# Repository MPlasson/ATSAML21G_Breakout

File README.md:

# ATSAML21G_Breakout
Breakout board for ATSAML21Gxx MCU

Now available on PCBS.io (sharing link): 
https://pcbs.io/share/rG9PZ

Bill of materials (BOM):

|  Designator  | Value |  Package description |
|     :---:      |     :---:      |     :---:      |
|R1 | 10k | 0805 |
|C1 | 100nF | 0805 |
|C2 | 1µF | 0805 |
|C3 | 100nF | 0805 |
|C4 | 1µF | 0805 |
|J1 | 21 pins | 0.1"/2.54mm header |
|J2 | 20 pins | 0.1"/2.54mm header |
|J3 | 5 pins | 0.1"/2.54mm header - JTAG connector |
|SW1 | K2-1107ST | Switch from LCSC.com |
|U1 | ATSAML21Gxx | MCU in LQFP48 package |

Here is the board once assembled:

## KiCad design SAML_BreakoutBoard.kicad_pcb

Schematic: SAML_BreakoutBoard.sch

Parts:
C1, C3: 100nF; C_0805
C2, C4: 1µF; C_0805
J1: Conn_01x21; Pin_Header_Straight_1x21_Pitch2.54mm
J2: Conn_01x20; Pin_Header_Straight_1x20_Pitch2.54mm
J3: JTAG; Pin_Header_Straight_1x05_Pitch2.54mm
R1: 10k; R_0805
SW1: K2-1107ST; SW_SPST_K2-1107ST
U1: ATSAML21G17B-AUT; LQFP-48_7x7mm_Pitch0.5mm

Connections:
/SWCLK: J1.5, J3.3, U1.45 (PA30)
/SWDIO: J1.4, J3.4, U1.46 (PA31)
/~RST: C1.1, J3.2, R1.2, SW1.1, U1.40 (~RESET)
GND: C1.2, C2.2, C3.2, C4.2, J1.21, J2.1, J3.5, SW1.2, U1.5 (GNDANA), U1.18 (GND), U1.35 (GND), U1.42 (GND)
unnamed: C2.1, U1.41 (VDDCORE)
unnamed: J1.2, U1.48 (PB03)
unnamed: J1.3, U1.47 (PB02)
unnamed: J1.6, U1.39 (PA27)
unnamed: J1.7, U1.38 (PB23)
unnamed: J1.8, U1.37 (PB22)
unnamed: J1.9, U1.34 (PA25)
unnamed: J1.10, U1.33 (PA24)
unnamed: J1.11, U1.32 (PA23)
unnamed: J1.12, U1.31 (PA22)
unnamed: J1.13, U1.30 (PA21)
unnamed: J1.14, U1.29 (PA20)
unnamed: J1.15, U1.28 (PA19)
unnamed: J1.16, U1.27 (PA18)
unnamed: J1.17, U1.26 (PA17)
unnamed: J1.18, U1.25 (PA16)
unnamed: J1.19, U1.24 (PA15)
unnamed: J1.20, U1.23 (PA14)
unnamed: J2.2, U1.22 (PA13)
unnamed: J2.3, U1.21 (PA12)
unnamed: J2.4, U1.20 (PB11)
unnamed: J2.5, U1.19 (PB10)
unnamed: J2.6, U1.16 (PA11)
unnamed: J2.7, U1.15 (PA10)
unnamed: J2.8, U1.14 (PA09)
unnamed: J2.9, U1.13 (PA08)
unnamed: J2.10, U1.12 (PA07)
unnamed: J2.11, U1.11 (PA06)
unnamed: J2.12, U1.10 (PA05)
unnamed: J2.13, U1.9 (PA04)
unnamed: J2.14, U1.8 (PB09)
unnamed: J2.15, U1.7 (PB08)
unnamed: J2.16, U1.4 (PA03)
unnamed: J2.17, U1.3 (PA02)
unnamed: J2.18, U1.2 (PA01)
unnamed: J2.19, U1.1 (PA00)
VCC: C3.1, C4.1, J1.1, J2.20, J3.1, R1.1, U1.6 (VDDANA), U1.17 (VDDIO), U1.36 (VDDIO), U1.44 (VDDIN)

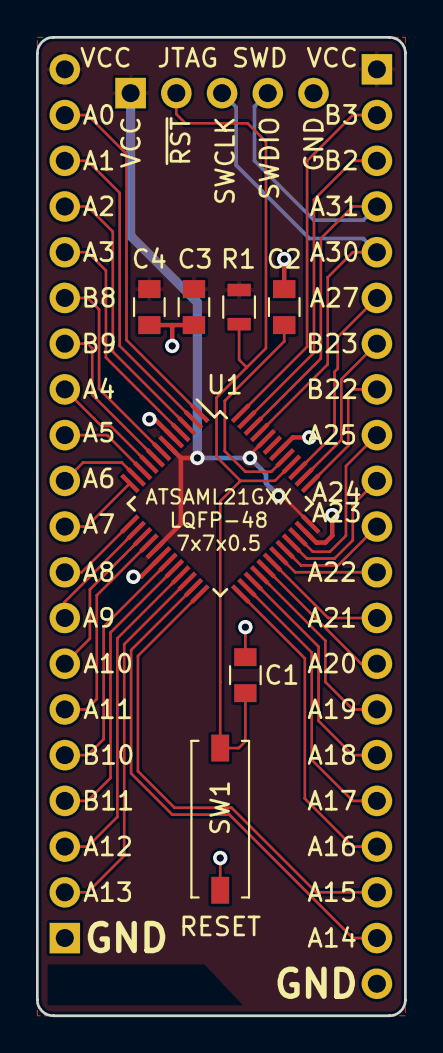
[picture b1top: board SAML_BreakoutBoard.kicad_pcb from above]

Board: 2 copper layers, 20.4 x 54.4 mm, 10 parts (0 on the bottom side), 41 nets.
